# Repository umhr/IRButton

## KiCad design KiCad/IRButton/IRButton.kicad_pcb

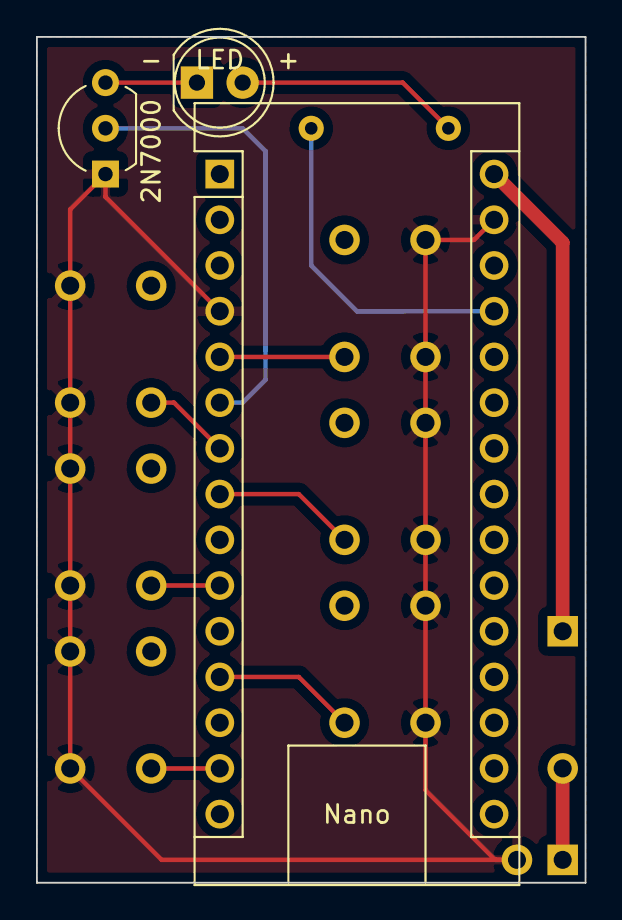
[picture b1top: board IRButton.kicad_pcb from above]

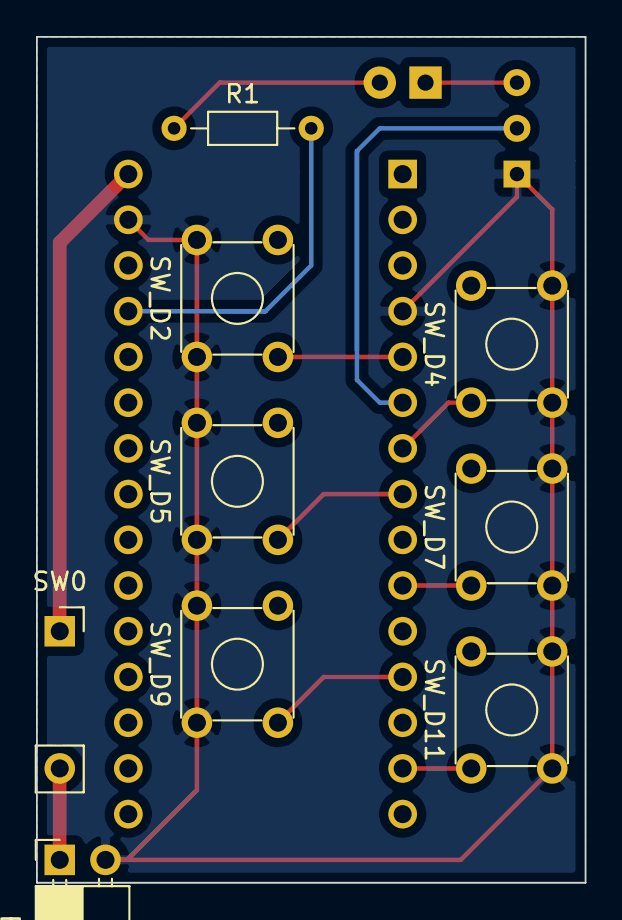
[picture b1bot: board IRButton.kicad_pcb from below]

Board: 2 copper layers, 30.5 x 47.0 mm, 12 parts (9 on the bottom side), 13 nets.

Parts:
2N7000: Q_NPN_EBC; TO-92L_Inline_Wide
BT1: Battery; PinSocket_1x02_P2.54mm_Horizontal
LED: LED; LED_D5.0mm_Clear
Nano: Arduino_Nano_v3.x; Arduino_Nano
R1: R; R_Axial_DIN0204_L3.6mm_D1.6mm_P7.62mm_Horizontal
SW0: SW_DPST_x2; PinSocket_1x02_P2.54mm_Vertical
SW_D2, SW_D4, SW_D5, SW_D7, SW_D9, SW_D11: SW_MEC_5E; SW_TH_Tactile_Omron_B3F-10xx

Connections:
GND: 2N7000.1, BT1.2, Nano.4, Nano.29, SW_D2.1, SW_D2.2, SW_D4.3, SW_D4.4, SW_D5.1, SW_D5.2, SW_D7.3, SW_D7.4, SW_D9.1, SW_D9.2, SW_D11.3, SW_D11.4
unnamed: Nano.5, SW_D2.3
unnamed: 2N7000.2, Nano.6
unnamed: Nano.7, SW_D4.1
unnamed: Nano.8, SW_D5.3
unnamed: Nano.10, SW_D7.1
unnamed: Nano.12, SW_D9.3
unnamed: Nano.14, SW_D11.1
unnamed: Nano.27, R1.2
unnamed: Nano.30, SW0.1
unnamed: BT1.1, SW0.2
unnamed: 2N7000.3, LED.1
unnamed: LED.2, R1.1

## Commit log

2022-02-27 配線間違い訂正
